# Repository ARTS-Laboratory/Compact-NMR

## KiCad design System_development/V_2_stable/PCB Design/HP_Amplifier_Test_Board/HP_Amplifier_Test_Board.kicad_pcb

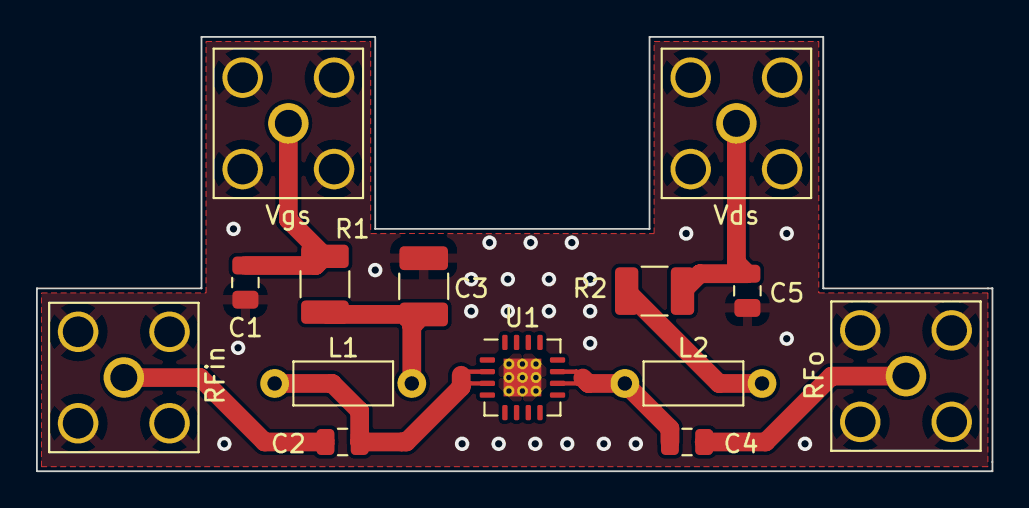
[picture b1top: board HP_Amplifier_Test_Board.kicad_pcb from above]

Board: 2 copper layers, 53.1 x 24.1 mm, 14 parts (0 on the bottom side), 9 nets.

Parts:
C1: 4.7uF; C_0805_2012Metric
C2, C4: 2400 pF; C_0805_2012Metric
C3: 0.01uF; C_1210_3225Metric_Pad1.33x2.70mm_HandSolder
C5: 4.7 uF; C_0805_2012Metric
L1, L2: 0.9 uH; L_Axial_L5.3mm_D2.2mm_P7.62mm_Horizontal_Vishay_IM-1
R1: 50; R_1210_3225Metric_Pad1.30x2.65mm_HandSolder
R2: 0; R_1210_3225Metric_Pad1.30x2.65mm_HandSolder
RFin: RFin; SMA_Amphenol_132203-12_Horizontal
RFo: RFo; SMA_Amphenol_132203-12_Horizontal
U1: NPA1003; QFN-16-1EP_4x4mm_P0.65mm_EP2.1x2.1mm_ThermalVias
Vds: Vds; SMA_Amphenol_132203-12_Horizontal
Vgs: Vgs; SMA_Amphenol_132203-12_Horizontal

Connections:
GND: C1.2, C3.2, C5.2, RFin.2 (Ext), RFo.2 (Ext), U1.17 (GND), Vds.2 (Ext), Vgs.2 (Ext)
unnamed: C1.1, R1.1, Vgs.1 (In)
unnamed: C2.1, RFin.1 (In)
unnamed: C2.2, L1.2, U1.2 (RFin/Vg), U1.3 (RFin/Vg)
unnamed: C3.1, L1.1, R1.2
unnamed: C4.1, RFo.1 (In)
unnamed: C4.2, L2.2, U1.10 (RFo/Vd), U1.11 (RFo/Vd)
unnamed: C5.1, R2.1, Vds.1 (In)
unnamed: L2.1, R2.2

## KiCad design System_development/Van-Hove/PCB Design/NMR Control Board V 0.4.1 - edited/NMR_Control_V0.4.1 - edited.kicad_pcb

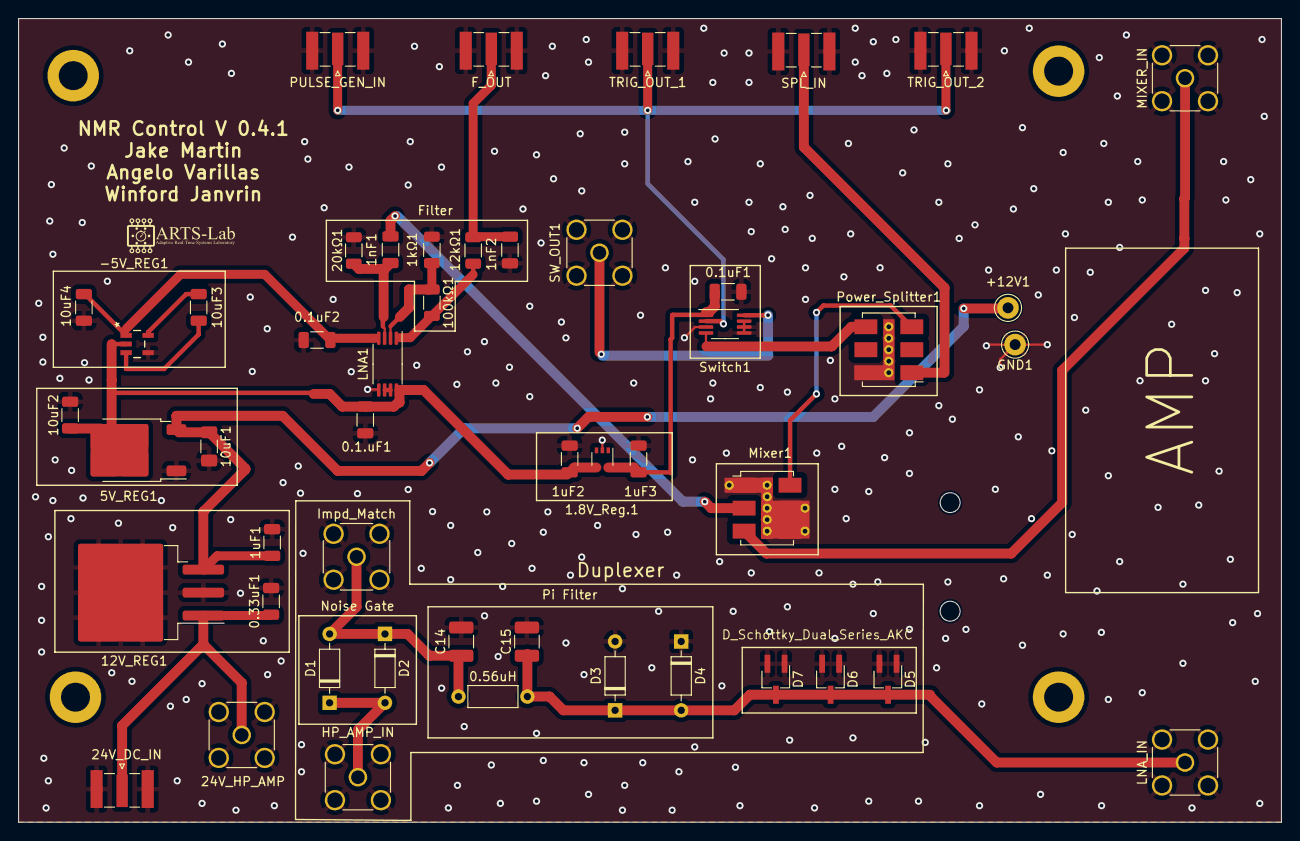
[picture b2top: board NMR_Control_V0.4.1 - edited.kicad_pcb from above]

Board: 2 copper layers, 139.7 x 88.9 mm, 49 parts (0 on the bottom side), 23 nets.

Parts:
0.1.uF1, 0.1uF2: 0.1uF; C_1206_3216Metric
0.1uF1: 0.1 uF; C_1206_3216Metric
0.33uF1: 0.33 uF; C_1206_3216Metric
0.56uH: L; L_Axial_L5.3mm_D2.2mm_P7.62mm_Horizontal_Vishay_IM-1
1.8V_Reg.1: NCP715-1.8V; SOT-353_SC-70-5
1kΩ1, 12kΩ1, 20kΩ1, 100kΩ1: R; R_1206_3216Metric
1nF1, 1nF2: C; C_1206_3216Metric
1uF1, 1uF2, 1uF3: 1 uF; C_1206_3216Metric
5V_REG1: NCP1117-5.0_TO252; TO-252-2
10uF1: 10 uF; C_1206_3216Metric_Pad1.33x1.80mm_HandSolder
10uF2, 10uF3, 10uF4: 10 uF; C_1206_3216Metric
12V_REG1: LM7812_TO220; TO-263-3_TabPin2
24V_DC_IN: Conn_Coaxial; SMA_Samtec_SMA-J-P-X-ST-EM1_EdgeMount
24V_HP_AMP: Conn_Coaxial; SMA_Amphenol_132291_Vertical
+12V1: Pin Hole; Pin_D1.0mm_L10.0mm_LooseFit
-5V_REG1: LM828M5; MF05A
C14, C15: C; C_1210_3225Metric_Pad1.33x2.70mm_HandSolder
D1, D2, D3, D4: 1N4148; D_DO-35_SOD27_P7.62mm_Horizontal
D5, D6, D7: D_Schottky_Dual_Series_AKC; TSOT-23_HandSoldering
F_OUT: Conn_Coaxial; SMA_Samtec_SMA-J-P-X-ST-EM1_EdgeMount
GND1: Pin Hole; Pin_D1.0mm_L10.0mm_LooseFit
HP_AMP_IN: Conn_Coaxial; SMA_Amphenol_132291_Vertical
Impd_Match: Conn_Coaxial; SMA_Amphenol_132134_Vertical
LNA1: LM4565; TSSOP-8_4.4x3mm_P0.65mm
LNA_IN: Conn_Coaxial; SMA_Amphenol_132291_Vertical
MIXER_IN: Conn_Coaxial; SMA_Amphenol_132291_Vertical
Mixer1: ADE-6; Mini-Circuits_CD542_LandPatternPL-052
PULSE_GEN_IN: Conn_Coaxial; SMA_Samtec_SMA-J-P-X-ST-EM1_EdgeMount
Power_Splitter1: ADP-2-1W; Mini-Circuits_CD636_LandPatternPL-035
SPL_IN: Conn_Coaxial; SMA_Samtec_SMA-J-P-X-ST-EM1_EdgeMount
SW_OUT1: Conn_Coaxial; SMA_Amphenol_132291_Vertical
Switch1: ADG901BRMZ; MSOP-8_3x3mm_P0.65mm
TRIG_OUT_1, TRIG_OUT_2: Conn_Coaxial; SMA_Samtec_SMA-J-P-X-ST-EM1_EdgeMount

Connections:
GND: 0.1.uF1.1, 0.1uF1.1, 0.1uF2.1, 0.33uF1.2, 1.8V_Reg.1.2 (GND), 1kΩ1.1, 1nF2.1, 1uF1.2, 1uF2.2, 1uF3.2, 5V_REG1.1 (GND), 10uF1.2, 10uF2.2, 10uF4.2, 12V_REG1.2 (GND), 20kΩ1.2, 24V_DC_IN.2 (Ext), 24V_HP_AMP.2 (Ext), -5V_REG1.4 (GND), C14.2, C15.2, D3.2 (A), D4.1 (K), D5.1 (A), D5.2 (K), D6.1 (A), D6.2 (K), D7.1 (A), D7.2 (K), F_OUT.2 (Ext), GND1.1 (In), HP_AMP_IN.2 (Ext), Impd_Match.2 (Ext), LNA1.5 (+IN2), LNA_IN.2 (Ext), MIXER_IN.2 (Ext), Mixer1.1 (GND), Mixer1.4 (GND), Mixer1.5 (GND), PULSE_GEN_IN.2 (Ext), Power_Splitter1.6 (GND), SPL_IN.2 (Ext), SW_OUT1.2 (Ext), Switch1.3 (GND), Switch1.5 (GND), Switch1.6 (GND), Switch1.7 (GND), TRIG_OUT_1.2 (Ext), TRIG_OUT_2.2 (Ext)
unnamed: 0.1uF1.2, 1.8V_Reg.1.5 (OUT), 1uF3.1, Switch1.1 (VDD)
unnamed: 0.33uF1.1, 12V_REG1.1 (VI), 24V_DC_IN.1 (In), 24V_HP_AMP.1 (In)
unnamed: 1uF1.1, 5V_REG1.3 (VI), 10uF1.1, 12V_REG1.3 (VO), +12V1.1 (In)
unnamed: 10uF3.1, -5V_REG1.5 (C1+)
unnamed: 10uF3.2, -5V_REG1.3 (C1-)
unnamed: 0.1uF2.2, 10uF4.1, -5V_REG1.1 (OUT), LNA1.4 (VEE)
unnamed: 0.1.uF1.2, 1.8V_Reg.1.4 (IN), 1uF2.1, 5V_REG1.2 (VO), 10uF2.1, -5V_REG1.2 (V+), LNA1.8 (VCC)
unnamed: 0.56uH.1, C14.1, D1.2 (A), D2.1 (K), Impd_Match.1 (In)
unnamed: D1.1 (K), D2.2 (A), HP_AMP_IN.1 (In)
unnamed: 0.56uH.2, C15.1, D3.1 (K), D4.2 (A), D5.3 (common), D6.3 (common), D7.3 (common), LNA_IN.1 (In)
unnamed: 1nF2.2, 12kΩ1.2, F_OUT.1 (In)
unnamed: 1nF1.1, 20kΩ1.1, LNA1.3 (+IN1)
unnamed: 1kΩ1.2, 100kΩ1.1, LNA1.2 (-IN1)
unnamed: LNA1.6 (-IN2), LNA1.7 (OUT2)
unnamed: 12kΩ1.1, 100kΩ1.2, LNA1.1 (OUT1)
unnamed: MIXER_IN.1 (In), Mixer1.3 (RF)
unnamed: 1nF1.2, Mixer1.2 (IF)
unnamed: Mixer1.6 (LO), Power_Splitter1.3 (PORT1)
unnamed: PULSE_GEN_IN.1 (In), Switch1.2 (CTRL), TRIG_OUT_1.1 (In), TRIG_OUT_2.1 (In)
unnamed: Power_Splitter1.4 (PORT2), Switch1.4 (RF1)
unnamed: Power_Splitter1.1 (SUM), SPL_IN.1 (In)
unnamed: SW_OUT1.1 (In), Switch1.8 (RF2)

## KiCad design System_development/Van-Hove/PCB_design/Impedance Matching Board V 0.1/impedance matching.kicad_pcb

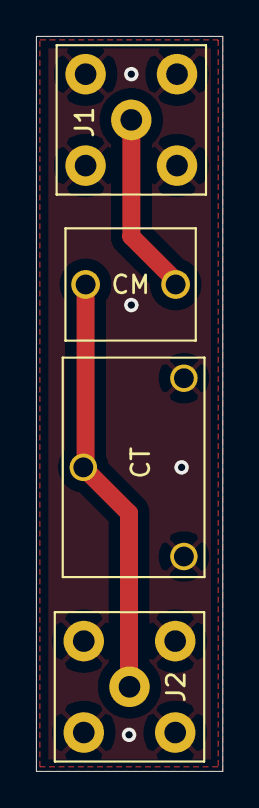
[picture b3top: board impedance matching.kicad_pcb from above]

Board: 2 copper layers, 10.4 x 40.8 mm, 4 parts (0 on the bottom side), 3 nets.

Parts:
CM: C_Variable; C_Rect_L7.0mm_W6.0mm_P5.00mm
CT: C_Trim_3_Leg; C_Trim_GZD10100
J1, J2: Conn_Coaxial; SMA_Amphenol_132203-12_Horizontal

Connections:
GND: CT.1, CT.2, J1.2, J2.2
unnamed: CM.1, CT.3, J2.1
unnamed: CM.2, J1.1

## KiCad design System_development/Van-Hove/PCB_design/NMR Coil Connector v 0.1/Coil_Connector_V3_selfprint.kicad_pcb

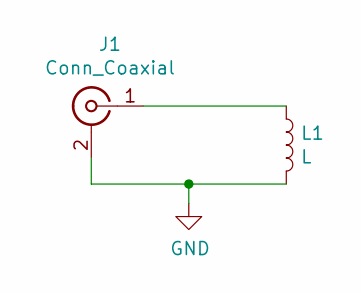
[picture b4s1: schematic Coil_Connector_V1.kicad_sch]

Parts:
J1: Conn_Coaxial; SMA_Amphenol_132203-12_Horizontal
L1: L; L_Coil

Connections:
GND: J1.2 (Ext), L1.2
unnamed: J1.1 (In), L1.1

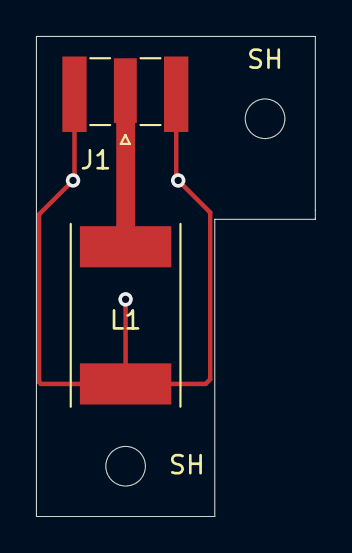
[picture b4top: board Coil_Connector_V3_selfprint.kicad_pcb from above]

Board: 2 copper layers, 15.5 x 26.7 mm, 4 parts (0 on the bottom side), 2 nets.

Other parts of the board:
SH: MountingHole_2.2mm_M2
SH#2: MountingHole_2.2mm_M2
